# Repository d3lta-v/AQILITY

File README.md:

by StatiX Electromechanics, a subsidiary company of [StatiX Industries](https://statixind.net)

# AQILITY (Air Quality Acquisition Ability)

This is the open source version of the AQILITY, the free, crowd-sourced software and hardware platform for air quality detection and the upload of data to the cloud. We were simply people who thought we could do something about the Singapore/Indonesian transboundary haze, and this is what we've made. Enjoy!

#### How to access live data from the currently deployed sensor:

**Live** data which is processed by the MATLAB program included in this repo can be accessed on ThingSpeak [here](https://thingspeak.com/channels/56281). NOTE: The picture below is NOT the actual live data.

Raw data (which may have errors) can be accessed [here](https://thingspeak.com/channels/31799), below is a sample of what to expect (this data is unprocessed and flawed, so please do not use this as official readings).

The AVR subsysem of this system uses a forked version of the [DustDuino](http://publiclab.org/wiki/dustduino) code base (licensed under the CC BY-SA 3.0 license) for an Arduino-compatible particulate sensing system. Big props to them for doing the best work in the world.

## Description:
This system collects real time data from the air with several onboard sensors and relays the data from the microcontroller to the Raspberry Pi which caches all the data collected. This data is periodically uploaded onto the ThingSpeak platform, which is then analysed by the MATLAB code and the new data inserted into another ThingSpeak channel to display the actual values.

The calculation from ug/m<sup>3</sup> to official AQI is a piecewise linear function provided by the EPA (research paper [here](http://www3.epa.gov/ttn/oarpg/t1/memoranda/rg701.pdf)). The system provides an LCD screen to display live unprocessed values for easy monitoring.

A full flowchart of the system can be seen as below:

1. Raspberry Pi sends a single unique character (a single dot, ".", ASCII code 46) to the microcontroller
2. Microcontroller has a cached copy of all the recent data taken over a certain timeframe and sends the cached data to the Pi. This data is already formatted in the CSV format.
3. Pi saves the data from the microcontroller into a CSV database.
4. The CSV database is read by another program and the data fed into the LCD driver on the GPIO to display air quality parameters on the LCD
5. Simultaneously, this data is sent by a HTTP POST request to the first ThingSpeak channel, which contains unprocessed data.
6. Data crunching takes place on the ThingSpeak platform with the MATLAB language, which calculates the correct AQI value using a piecewise linear function defined by the EPA.
7. The processed data is sent to the second ThingSpeak channel which houses all the processed data.

#### Features:

1. Has an LCD to display the air quality parameters dynamically on the sensor board itself
2. Automatically uploads air quality data to the cloud (ThingSpeak.com)
3. Relies on a Arduino-Raspberry Pi hybrid to achieve both long term data storage and better data transfer options such as through a cellular/3G USB dongle
4. Detects some of the most common airborne pollutants and chemicals (PM10, PM2.5, H2S, CO, VOCs) for the computation of the overall pollutant indices
5. The system has an initial waiting time, to wait for the AVR and the sensors to initialize and self-calibrate before taking readings.

## Availability:
This system is only tested on Raspberry Pis and the ATmega328P chip. There will be no guarentees that the same code (built on the Arduino platform) will run properly on other Arduino platforms or even on other AVRs such as the XMega series. The ribbon cable connector on the offical board is customized for Raspberry Pi + series ONLY, but you can manually pinout the connector for the old 28-pin GPIO.

## Author(s):
* Chief Designer; Programmer: Pan Ziyue
* R&D/Scientific Inquiry: Chow Zi Jie & Rachit Agrwal
* The awesome open source folks at Adafruit and the [DustDuino Development Team](http://publiclab.org/wiki/dustduino)

## Caveats:
* Requires for the Raspberry Pi's UART port on the GPIO to be freed. More info [here](http://www.hobbytronics.co.uk/raspberry-pi-serial-port)
* The code on the AVR seems to have a discrepancy of a factor of 10 for the PM2.5 concentration, which is then manually rectified by the MATLAB code. There may be a serious underlying problem with the original DustDuino code for the calculation of concentration, or lack of calibration of the sensor (which is supposed to be factory calibrated)
* The use of a Raspberry Pi enforces the use of a 5V/3.3V logic level shifter to avoid damaging the Pi.
* The gas sensors have NO calibration, which means that there is currently no logic implemented for the equation of output voltage of gas sensors to corresponding concentrations of gases.
* The Python code on the Raspberry Pi does not automatically archive or delete old data, and requires manual work to clear old data. This is a possible area of improvement and we welcome you to submit a pull request to implement such a feature.
* Dependencies must be manually installed and the GPIO port manually configured, which reduces code reusability and portability. Suggest making a single shell script to accomplish all of that.
* Python scripts must be pre-specified in `/etc/rc.local` for it to automatically start when the Raspberry Pi is booted up.

##  Dependencies:
* [Adafruit_Python_CharLCD](https://github.com/adafruit/Adafruit_Python_CharLCD)
* [DHT11 Library](http://playground.arduino.cc/Main/DHT11Lib)
* PySerial (install with `sudo pip3 install pyserial`)
* [httplib2](https://github.com/jcgregorio/httplib2)

## License:
<br />This work is licensed under a <a rel="license" href="http://creativecommons.org/licenses/by-sa/3.0/">Creative Commons Attribution-ShareAlike 3.0 Unported License</a>.

Copyright (C) StatiX Industries 2014-2016

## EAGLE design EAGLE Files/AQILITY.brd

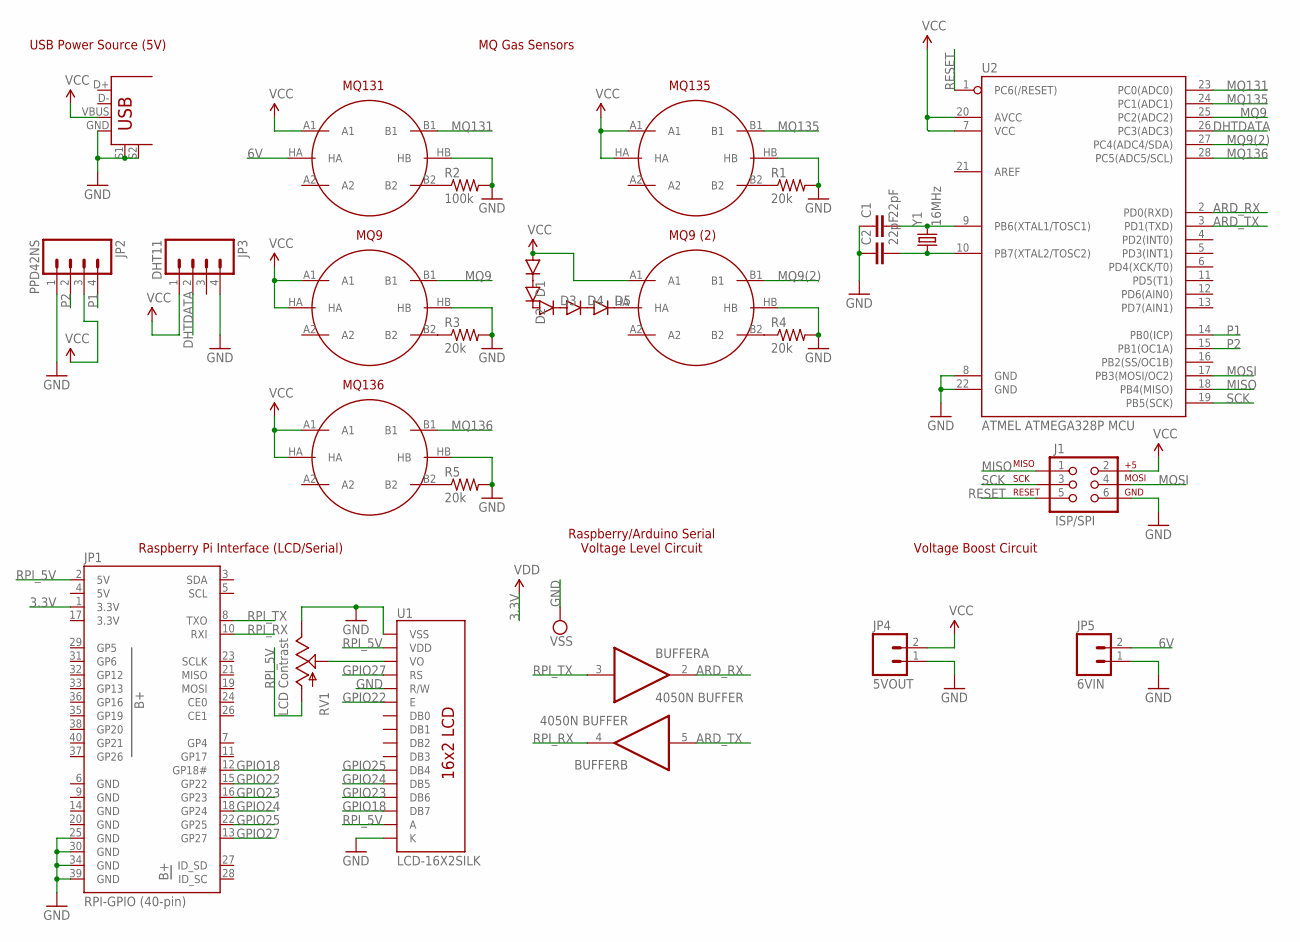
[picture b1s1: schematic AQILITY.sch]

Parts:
BUFFER: 4050N BUFFER; DIL16
C1, C2: 22pF; CAP-PTH-SMALLEZ
D1, D2, D3, D4, D5: DIODEKIT2; DIODE-1N4001-KIT
J1: ISP/SPI; 2X3
JP1: RPI-GPIO (40-pin); 2X20-SHROUDED
JP2: PPD42NS; 1X04
JP3: DHT11; 1X04
JP4: 5VOUT; 1X02
JP5: 6VIN; 1X02
MQ9, MQ9(2), MQ131, MQ135, MQ136: METHANE_SENSOR; MQ-3
R1, R3, R4, R5: 20k; AXIAL-0.4
R2: 100k; AXIAL-0.4
RV1: LCD Contrast; 3362U
U1: LCD-16X2SILK; LCD-16X2
U2: ATMEL ATMEGA328P MCU; DIL28-3
U$5: USB/5V; USB-B-PTH
Y1: 16MHz; HC49U-V

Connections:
3.3V: BUFFER.1 (VDD), JP1.1 (3.3V), JP1.17 (3.3V)
5V: JP1.4 (5V)
6V: JP5.2, MQ131.HA
ARD_RX: BUFFER.2 (O), U2.2 (PD0(RXD))
ARD_TX: BUFFER.5 (I), U2.3 (PD1(TXD))
DHTDATA: JP3.2, U2.26 (PC3(ADC3))
GND: BUFFER.8 (VSS), C1.1, C2.1, J1.6, JP1.6 (GND), JP1.9 (GND), JP1.14 (GND), JP1.20 (GND), JP1.25 (GND), JP1.30 (GND), JP1.34 (GND), JP1.39 (GND), JP2.1, JP3.4, JP4.1, JP5.1, MQ9.HB, MQ9(2).HB, MQ131.HB, MQ135.HB, MQ136.HB, R1.P$2 (2), R2.P$2 (2), R3.P$2 (2), R4.P$2 (2), R5.P$2 (2), RV1.P$1 (E), U1.1 (VSS), U1.5 (R/W), U1.16 (K), U2.8 (GND), U2.22 (GND), U$5.GND, U$5.S1, U$5.S2
GPIO18: JP1.12 (GP18#), U1.14 (DB7)
GPIO22: JP1.15 (GP22), U1.6 (E)
GPIO23: JP1.16 (GP23), U1.13 (DB6)
GPIO24: JP1.18 (GP24), U1.12 (DB5)
GPIO25: JP1.22 (GP25), U1.11 (DB4)
GPIO27: JP1.13 (GP27), U1.4 (RS)
MISO: J1.1, U2.18 (PB4(MISO))
MOSI: J1.4, U2.17 (PB3(MOSI/OC2))
MQ9: MQ9.B1, U2.25 (PC2(ADC2))
MQ9(2): MQ9(2).B1, U2.27 (PC4(ADC4/SDA))
MQ131: MQ131.B1, U2.23 (PC0(ADC0))
MQ135: MQ135.B1, U2.24 (PC1(ADC1))
MQ136: MQ136.B1, U2.28 (PC5(ADC5/SCL))
unnamed: RV1.P$2 (S), U1.3 (VO)
unnamed: C1.2, U2.9 (PB6(XTAL1/TOSC1)), Y1.2
unnamed: C2.2, U2.10 (PB7(XTAL2/TOSC2)), Y1.1
unnamed: D1.C, D2.A
unnamed: D2.C, D3.A
unnamed: D3.C, D4.A
unnamed: D5.C, MQ9(2).HA
unnamed: D4.C, D5.A
unnamed: MQ136.B2, R5.P$1 (1)
unnamed: MQ135.B2, R1.P$1 (1)
unnamed: MQ9.B2, R3.P$1 (1)
unnamed: MQ131.B2, R2.P$1 (1)
unnamed: MQ9(2).B2, R4.P$1 (1)
P1: JP2.4, U2.14 (PB0(ICP))
P2: JP2.2, U2.15 (PB1(OC1A))
RESET: J1.5, U2.1 (PC6(/RESET))
RPI_5V: JP1.2 (5V), RV1.P$3 (A), U1.2 (VDD), U1.15 (A)
RPI_RX: BUFFER.4 (O), JP1.10 (RXI)
RPI_TX: BUFFER.3 (I), JP1.8 (TXO)
SCK: J1.3, U2.19 (PB5(SCK))
VCC: D1.A, J1.2, JP2.3, JP3.1, JP4.2, MQ9.A1, MQ9.HA, MQ9(2).A1, MQ131.A1, MQ135.A1, MQ135.HA, MQ136.A1, MQ136.HA, U2.7 (VCC), U2.20 (AVCC), U$5.VBUS

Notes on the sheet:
MQ135
MQ131
MQ9
MQ9 (2)
MQ136
Voltage Boost Circuit
Raspberry Pi Interface (LCD/Serial)
MQ Gas Sensors
USB Power Source (5V)
Raspberry/Arduino Serial Voltage Level Circuit

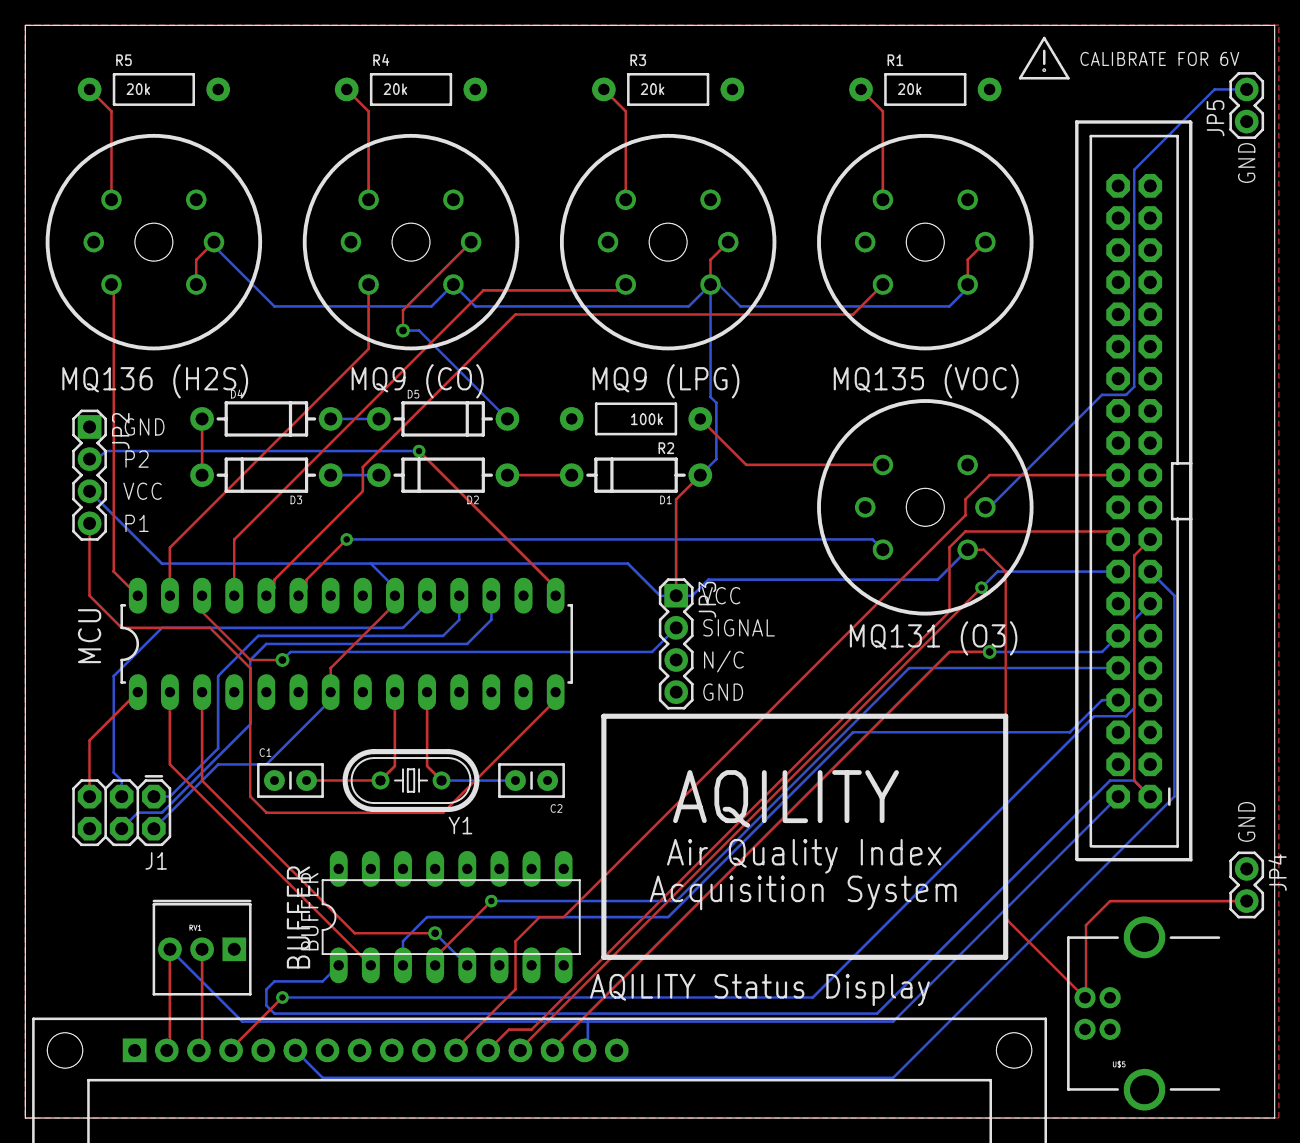
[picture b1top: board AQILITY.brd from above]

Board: 2 copper layers, 98.7 x 86.3 mm, 29 parts (0 on the bottom side), 40 nets.

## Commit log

2015-09-24 updated README with pictures
2015-09-24 fixed image assets
2015-09-24 changed the position of the logo
2015-09-24 new assets and better README
2015-09-24 reduced size of OSHW logo
2015-09-24 double check size of OSHW logo
2015-09-24 updated README to be cleaner
2015-09-24 added live data to README
2015-09-24 reverted to non-iframe based README
2015-09-24 added warning
2017-04-27 Fixed issues with README
2022-01-05 readme updated

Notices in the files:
parts and their libraries:
SparkFun-Capacitors: Licensing: Creative Commons ShareAlike 4.0 International - https://creativecommons.org/licenses/by-sa/4.0
